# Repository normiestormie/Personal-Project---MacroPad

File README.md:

# Personal-Project---MacroPad
My first ever personal project - a simple MacroPad based off HackClub Blueprint's MAcroPad Tutorial. I started this project because I wanted a sort of easy-ish first project to give me some more experience in STEM. Next year I am going to college so I think that this will help me learn the fundamentals and give me more experience on creating things. I also plan on actually using this mainly for using shortcuts on my computer. I want to make it so there is a ctrl+c and ctrl+v shortcut on two of the keys for sure. I also want to make something animated to put on the OLED display that will be running when I plug the MacroPad in. The rotary encoder will also be used for 

Hopefully it works!

BOM for parts: 
- 5x white blank DSA keycaps
- 1x EC11 Rotary encoder
- 1 unsoldered Seeed XIAO RP2040
- 1x 0.91 inch OLED display
- 4x M3x16mm screws
- 4x M3x5mx4mm heatset inserts

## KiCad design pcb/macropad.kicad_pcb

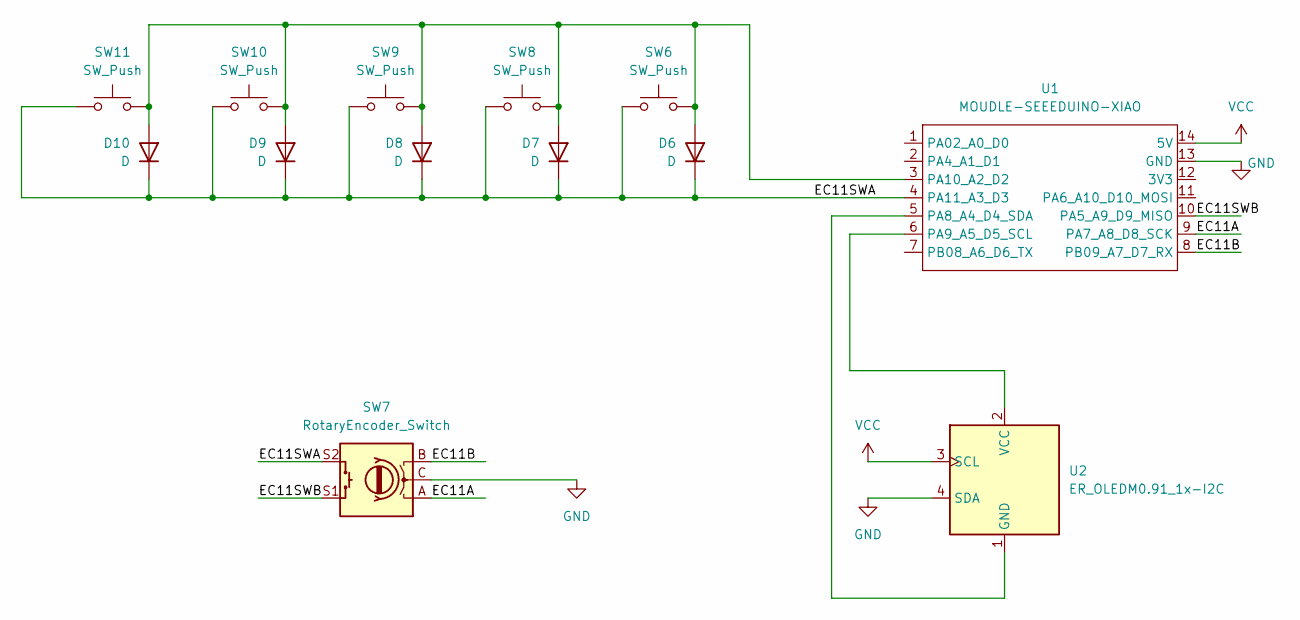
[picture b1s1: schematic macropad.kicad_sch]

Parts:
D6, D7, D8, D9, D10: D; D_A-405_P7.62mm_Horizontal
SW6, SW8, SW9, SW10, SW11: SW_Push; SW_Cherry_MX_1.00u_PCB
SW7: RotaryEncoder_Switch; RotaryEncoder_Alps_EC11E-Switch_Vertical_H20mm_CircularMoun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
U1: MOUDLE-SEEEDUINO-XIAO; XIAO-Generic-Hybrid-14P-2.54-21X17.8MM
U2: ER_OLEDM0.91_1x-I2C

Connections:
/EC11A: SW7.A, U1.9 (PA7_A8_D8_SCK)
/EC11B: SW7.B, U1.8 (PB09_A7_D7_RX)
/EC11SWA: D6.1 (K), D7.1 (K), D8.1 (K), D9.1 (K), D10.1 (K), SW6.2, SW7.S2, SW8.2, SW9.2, SW10.2, SW11.2, U1.4 (PA11_A3_D3)
/EC11SWB: SW7.S1, U1.10 (PA5_A9_D9_MISO)
GND: SW7.C, U1.13 (GND), U2.4 (SDA)
unnamed: D6.2 (A), D7.2 (A), D8.2 (A), D9.2 (A), D10.2 (A), SW6.1, SW8.1, SW9.1, SW10.1, SW11.1, U1.3 (PA10_A2_D2)
unnamed: U1.5 (PA8_A4_D4_SDA), U2.1 (GND)
unnamed: U1.6 (PA9_A5_D5_SCL), U2.2 (VCC)
VCC: U1.14 (5V), U2.3 (SCL)

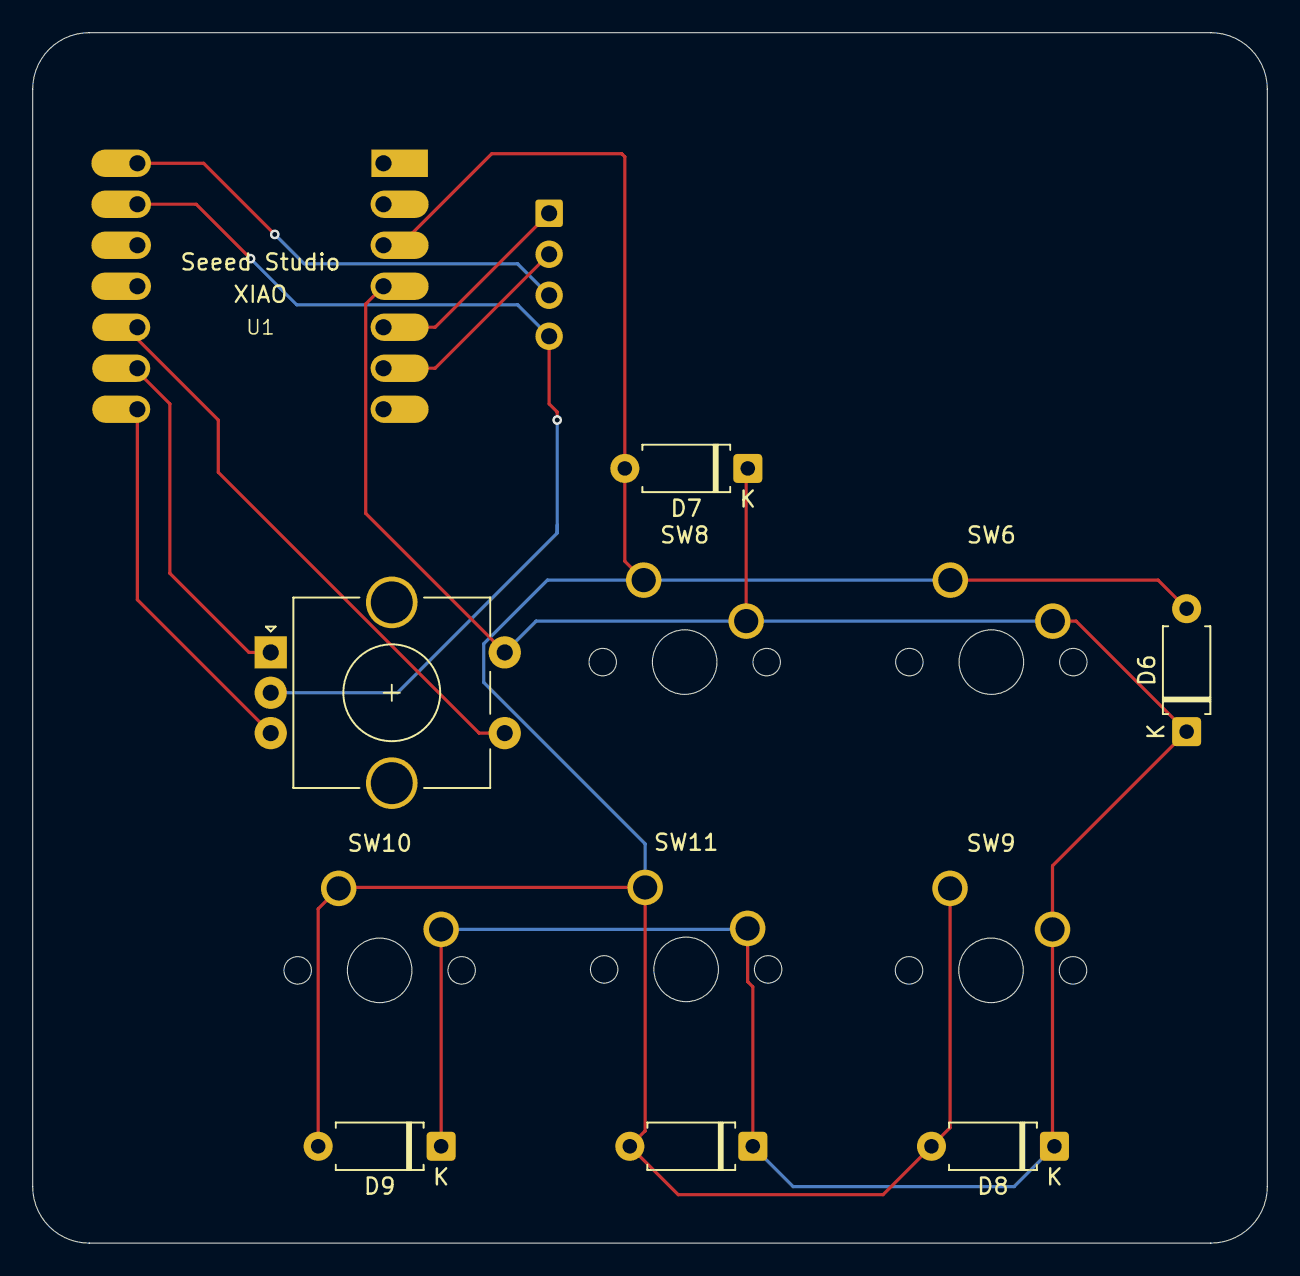
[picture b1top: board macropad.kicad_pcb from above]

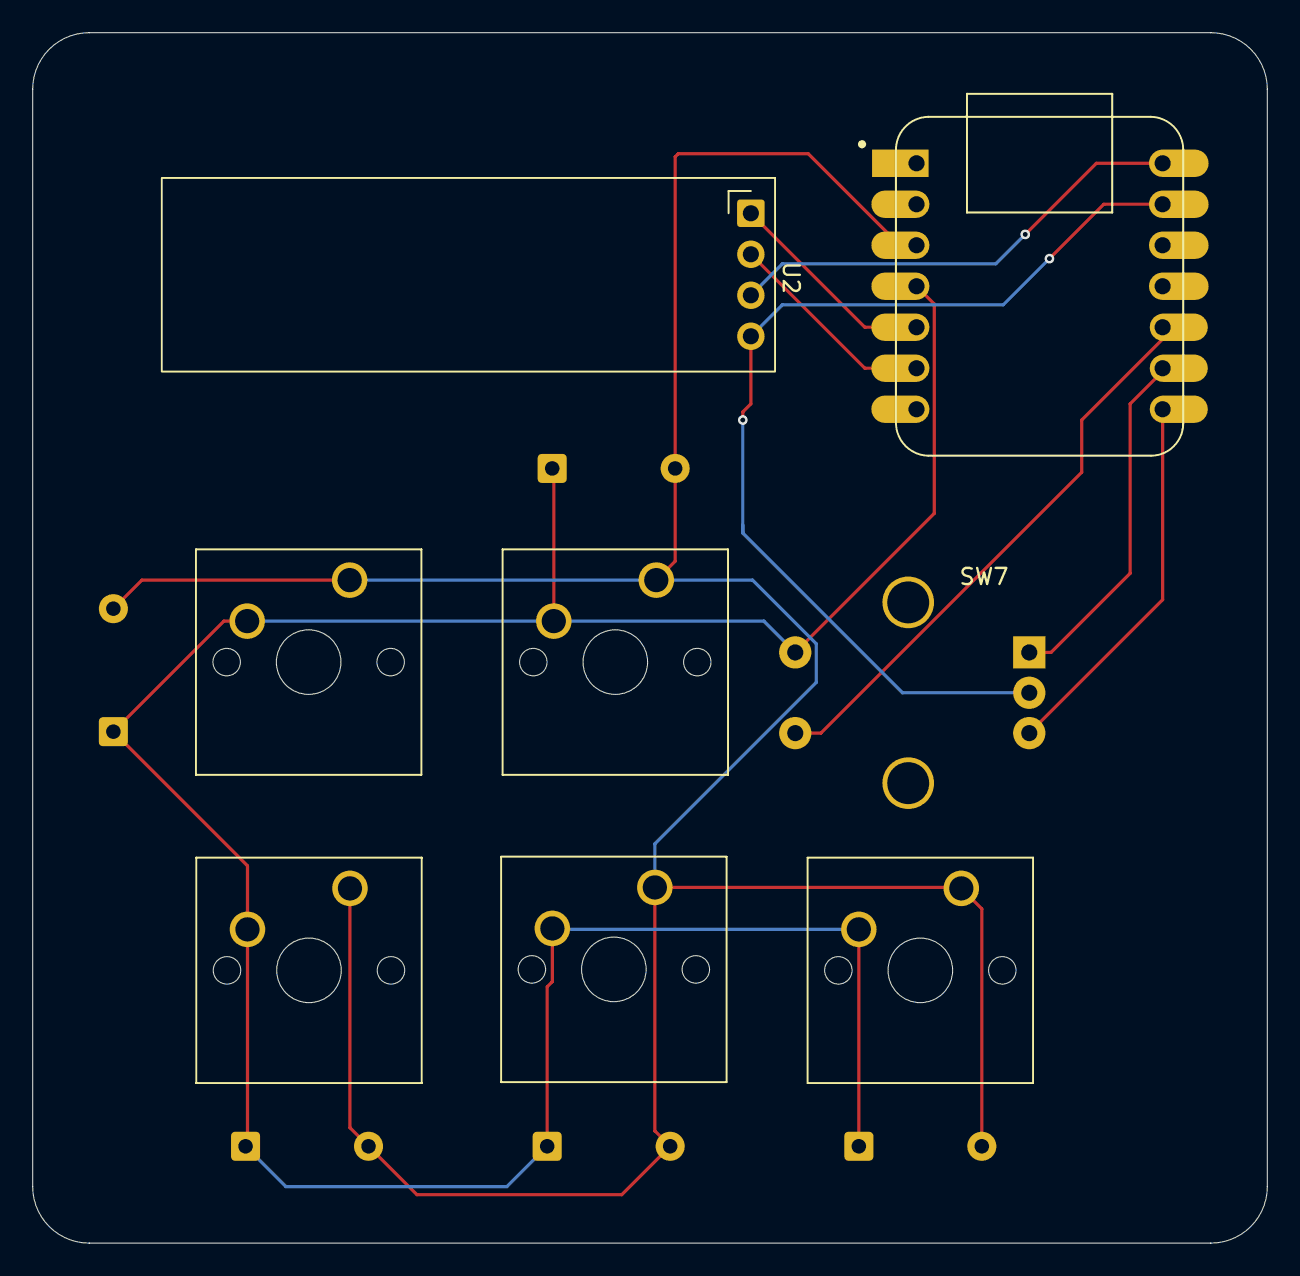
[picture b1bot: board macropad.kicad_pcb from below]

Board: 2 copper layers, 76.5 x 75.0 mm, 13 parts (7 on the bottom side), 9 nets.

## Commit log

2026-03-31 Create CAD
2026-03-31 Create MAIN
2026-03-31 Create PCB
2026-03-31 Create prod
2026-03-31 Rename MAIN to MAIN.py
2026-03-31 Create image
2026-03-31 Update image
